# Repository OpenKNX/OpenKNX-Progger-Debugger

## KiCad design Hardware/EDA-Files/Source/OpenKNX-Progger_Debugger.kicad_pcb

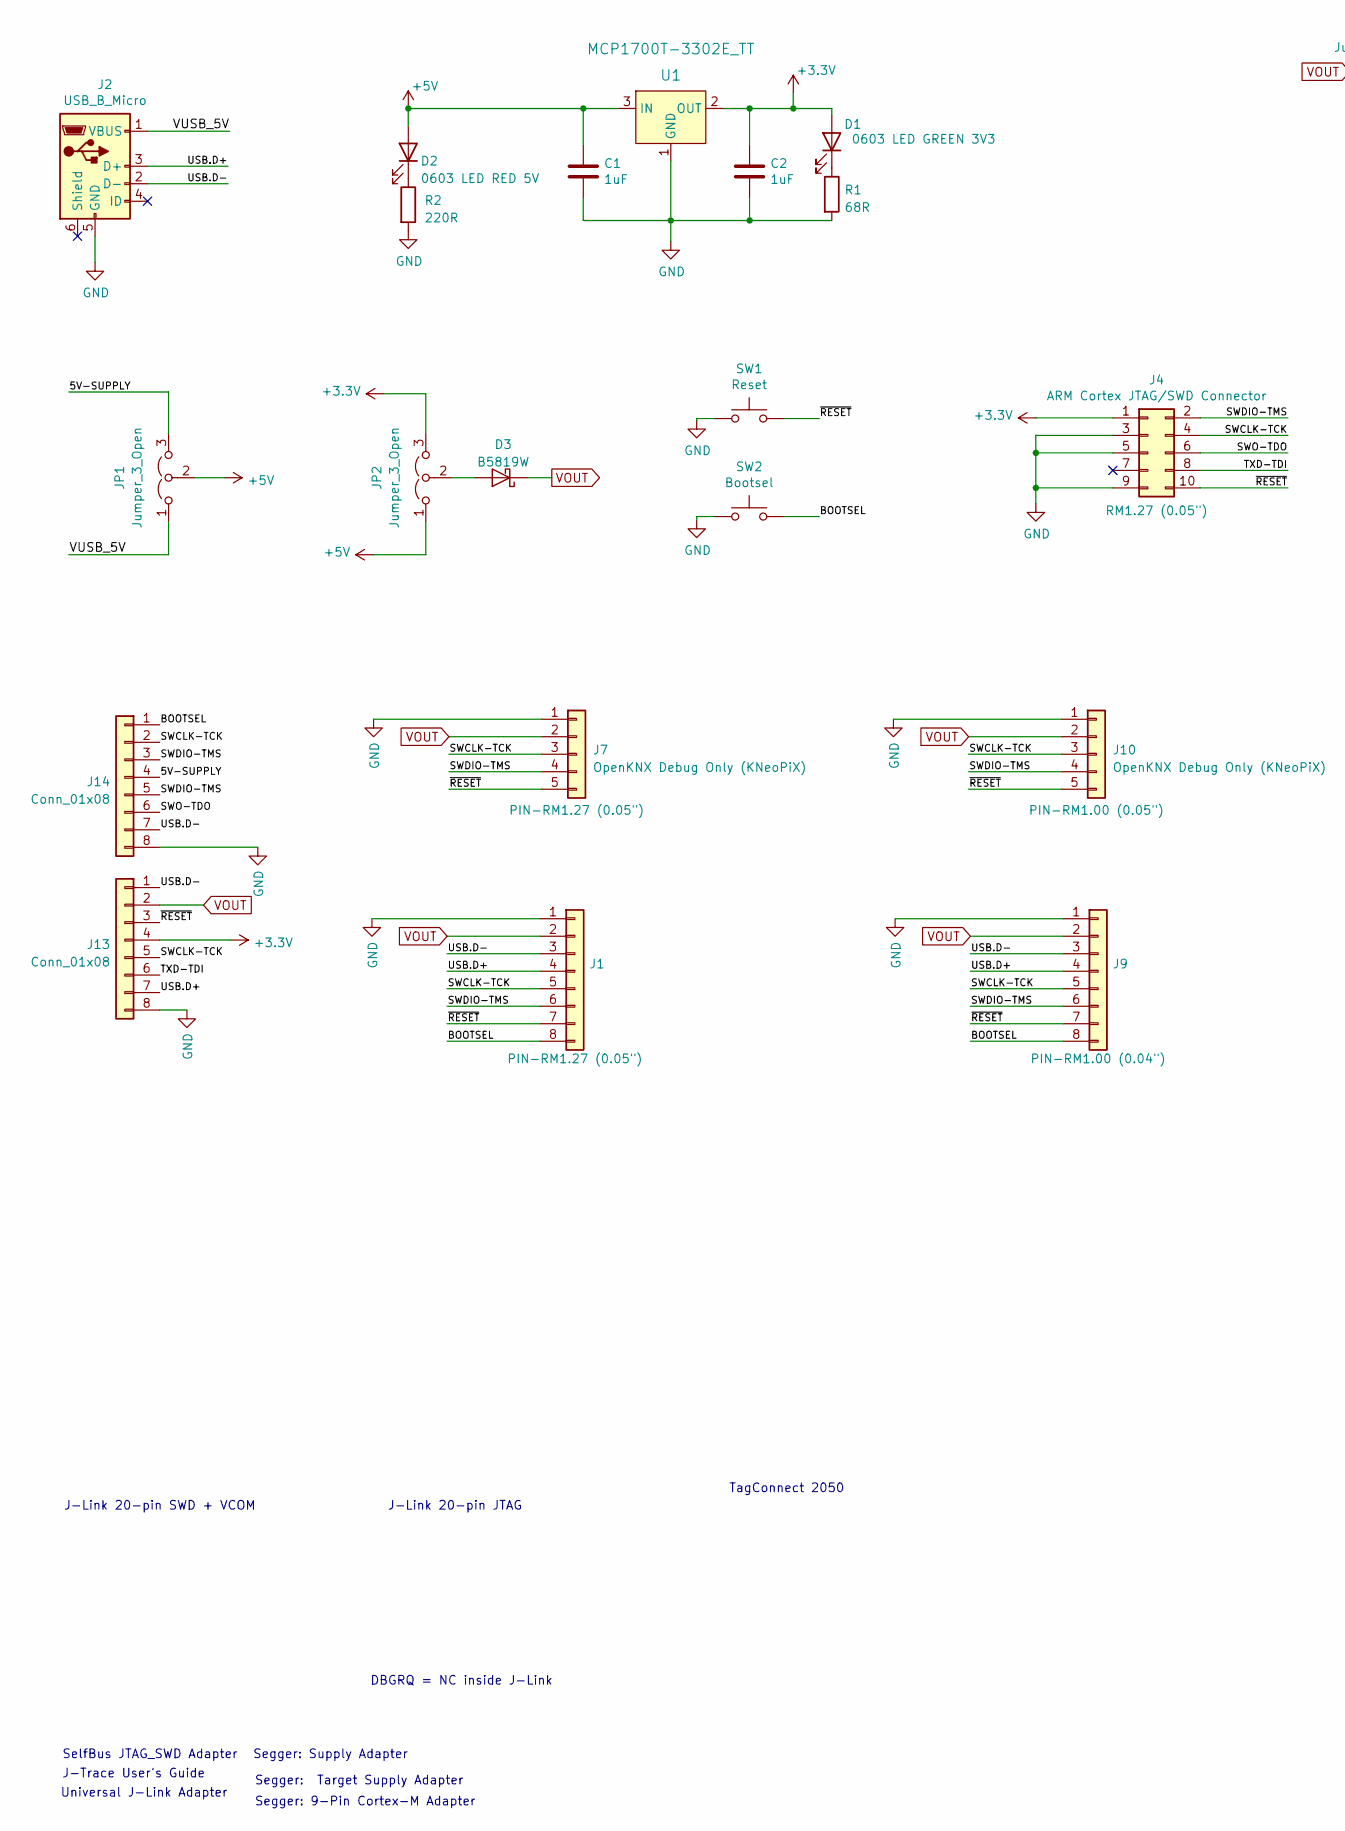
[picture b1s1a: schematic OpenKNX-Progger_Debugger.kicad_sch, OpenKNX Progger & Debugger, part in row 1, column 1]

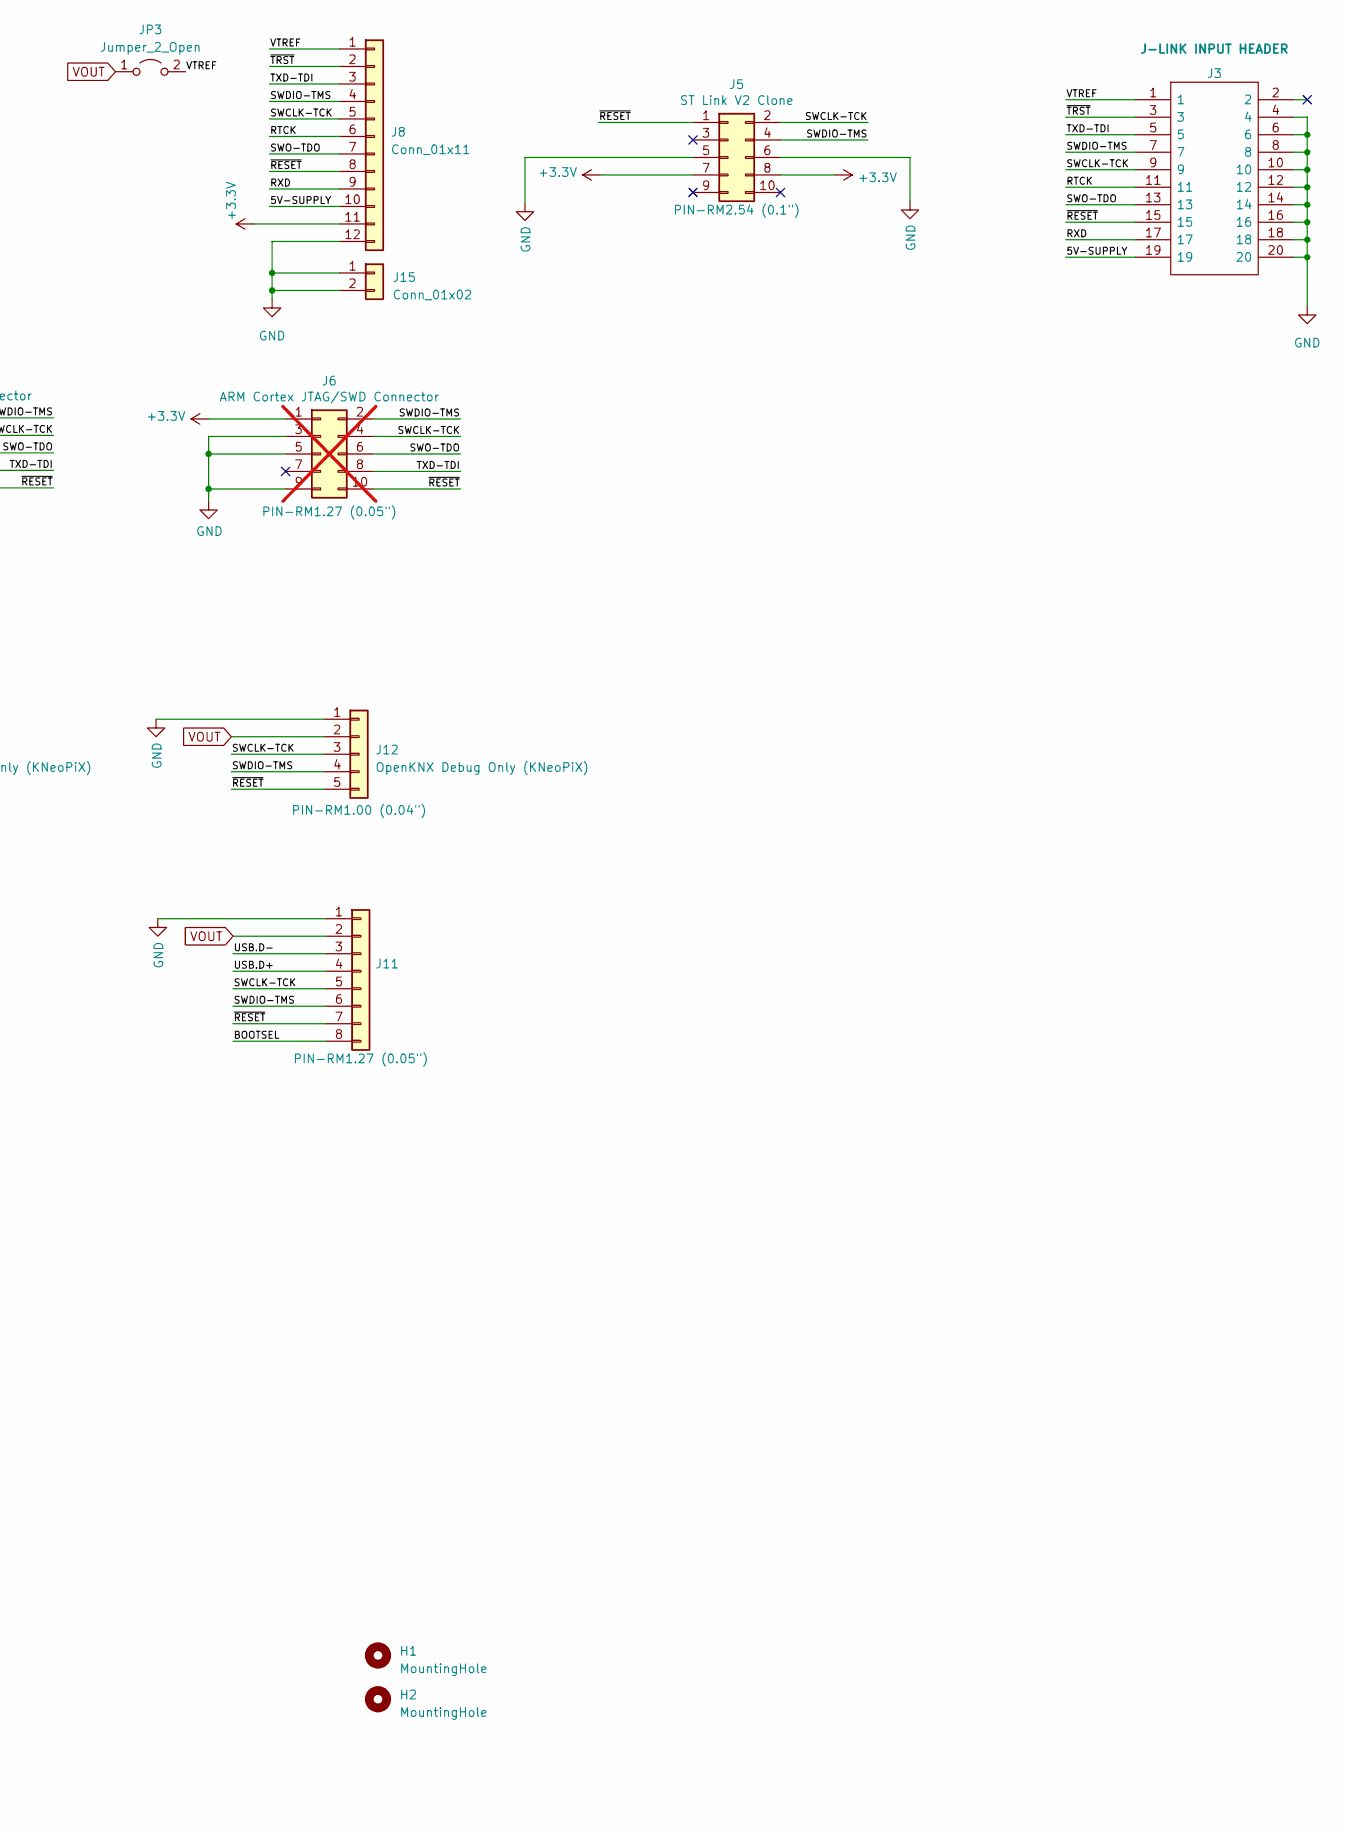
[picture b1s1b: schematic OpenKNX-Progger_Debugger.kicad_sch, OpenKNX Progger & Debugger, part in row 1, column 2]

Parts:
C1, C2: 1uF; C_0201_0603Metric_Pad0.64x0.40mm_HandSolder
D1: 0603 LED GREEN 3V3; LED_0201_0603Metric
D2: 0603 LED RED 5V; LED_0201_0603Metric
D3: B5819W; D_SOD-123; Part Number B140HW-7; JLCPCB ID C134429
H1, H2: MountingHole; MountingHole_2.1mm
J1, J11: OpenKNX Progger / Debugger Connection; PinSocket_1x08_P1.27mm_Vertical
J2: USB_B_Micro; USB_Micro-B_JING_C10418
J3: SFH11-PBPC-D10-RA-BK; IDC-Header_2x10_P2.54mm_Vertical; Manufacturer_Part_Number SFH11-PBPC-D10-RA-BK
J4: ARM Cortex JTAG/SWD Connector; PinHeader_2x05_P1.27mm_Vertical
J5: ST Link V2 Clone; IDC-Header_2x05_P2.54mm_Vertical
J6: ARM Cortex JTAG/SWD Connector; PinHeader_2x05_P1.27mm_Vertical; not fitted
J7, J12: OpenKNX Debug Only (KNeoPiX); PinSocket_1x05_P1.27mm_Vertical
J8: Conn_01x11; PinHeader_1x12_P2.54mm_Vertical
J9: OpenKNX Progger / Debugger Connection; JST_SHL_SM08B-SHLS-TF_1x08-1MP_P1.00mm_Horizontal
J10: OpenKNX Debug Only (KNeoPiX); JST_SHL_SM05B-SHLS-TF_1x05-1MP_P1.00mm_Horizontal
J13: Conn_01x08; JUMPER_SMD_1x8_NO_CUTS
J14: Conn_01x08; JUMPER_SMD_1x8_CUTS
J15: Conn_01x02; PinHeader_1x02_P2.54mm_Vertical
JP1, JP2: Jumper_3_Open; PinHeader_1x03_P1.27mm_Vertical
JP3: Jumper_2_Open; PinHeader_1x02_P1.27mm_Vertical
R1: 68R_0603_0.1%; R_0201_0603Metric
R2: 220R_0603_0.1%; R_0201_0603Metric
SW1: Reset; SW_Push_Xunpu_TS-1089S_Handsolder
SW2: Bootsel; SW_Push_Xunpu_TS-1089S_Handsolder
U1: MCP1700T-3302E_TT; SOT-23-3; MPN MCP1700T-3302E/TT; Digi-Key_PN MCP1700T3302ETTCT-ND

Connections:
+3.3V: C2.1, D1.2 (A), J4.1, J5.7, J5.8, J6.1, J8.11, J13.4, JP2.3 (B), U1.2 (OUT)
+5V: C1.1, D2.2 (A), JP1.2 (C), JP2.1 (A), U1.3 (IN)
/5V-SUPPLY: J3.19, J8.10, J14.4, JP1.3 (B)
/BOOTSEL: J1.8, J9.8, J11.8, J14.1, SW2.2
/RTCK: J3.11, J8.6
/RXD: J3.17, J8.9
/SWCLK-TCK: J1.5, J3.9, J4.4, J5.2, J7.3, J8.5, J9.5, J10.3, J11.5, J12.3, J13.5, J14.2
/SWDIO-TMS: J1.6, J3.7, J4.2, J5.4, J7.4, J8.4, J9.6, J10.4, J11.6, J12.4, J14.3, J14.5
/SWO-TDO: J1.13, J3.13, J4.6, J6.6, J8.7, J14.6
/TXD-TDI: J3.5, J4.8, J8.3, J13.6
/USB.D+: J1.4, J2.3 (D+), J9.4, J11.4, J13.7
/USB.D-: J1.3, J2.2 (D-), J9.3, J11.3, J13.1, J14.7
/VTREF: J3.1, J8.1, JP3.2 (B)
/VUSB_5V: J2.1 (VBUS), JP1.1 (A)
/~RESET: J1.7, J3.15, J4.10, J5.1, J7.5, J8.8, J9.7, J10.5, J11.7, J12.5, J13.3, SW1.2
/~TRST: J3.3, J8.2
GND: C1.2, C2.2, J1.1, J2.5 (GND), J3.4, J3.6, J3.8, J3.10, J3.12, J3.14, J3.16, J3.18, J3.20, J4.3, J4.5, J4.9, J5.5, J5.6, J7.1, J8.12, J9.1, J10.1, J11.1, J12.1, J13.8, J14.8, J15.1, J15.2, R1.2, R2.2, SW1.1, SW2.1, U1.1 (GND)
unnamed: D1.1 (K), R1.1
unnamed: D2.1 (K), R2.1
unnamed: D3.2 (A), JP2.2 (C)
VOUT: D3.1 (K), J1.2, J7.2, J9.2, J10.2, J11.2, J12.2, J13.2, JP3.1 (A)

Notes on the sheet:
DBGRQ = NC inside J-Link
J-Trace User's Guide
J-Link 20-pin SWD + VCOM
Segger: Target Supply Adapter
Segger: Supply Adapter
SelfBus JTAG_SWD Adapter
Segger: 9-Pin Cortex-M Adapter
J-Link 20-pin JTAG
Universal J-Link Adapter
TagConnect 2050

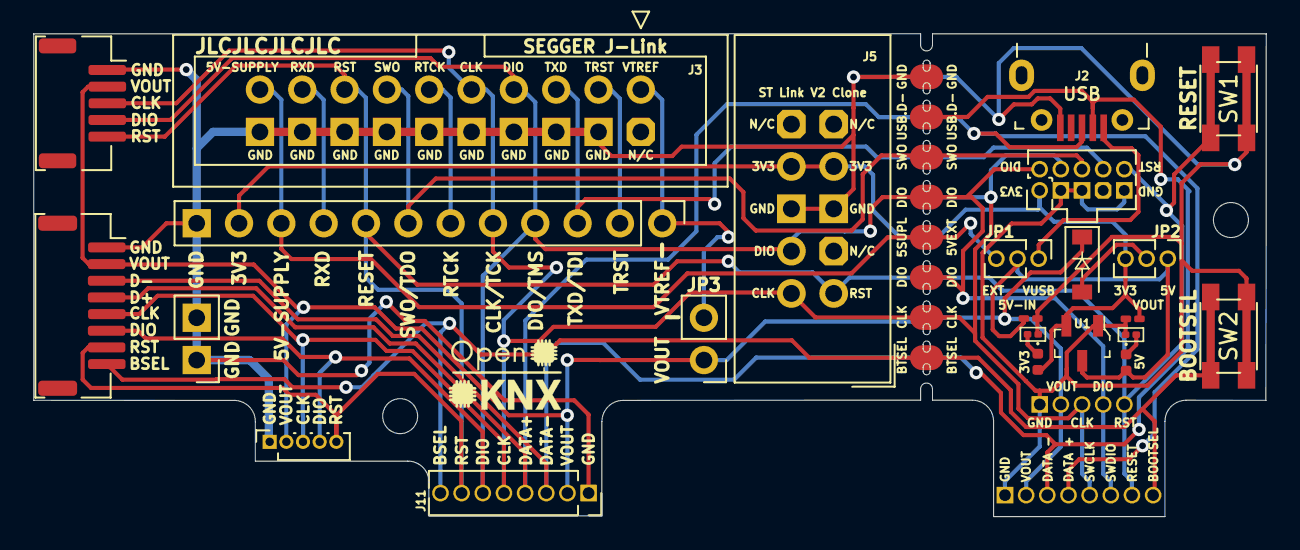
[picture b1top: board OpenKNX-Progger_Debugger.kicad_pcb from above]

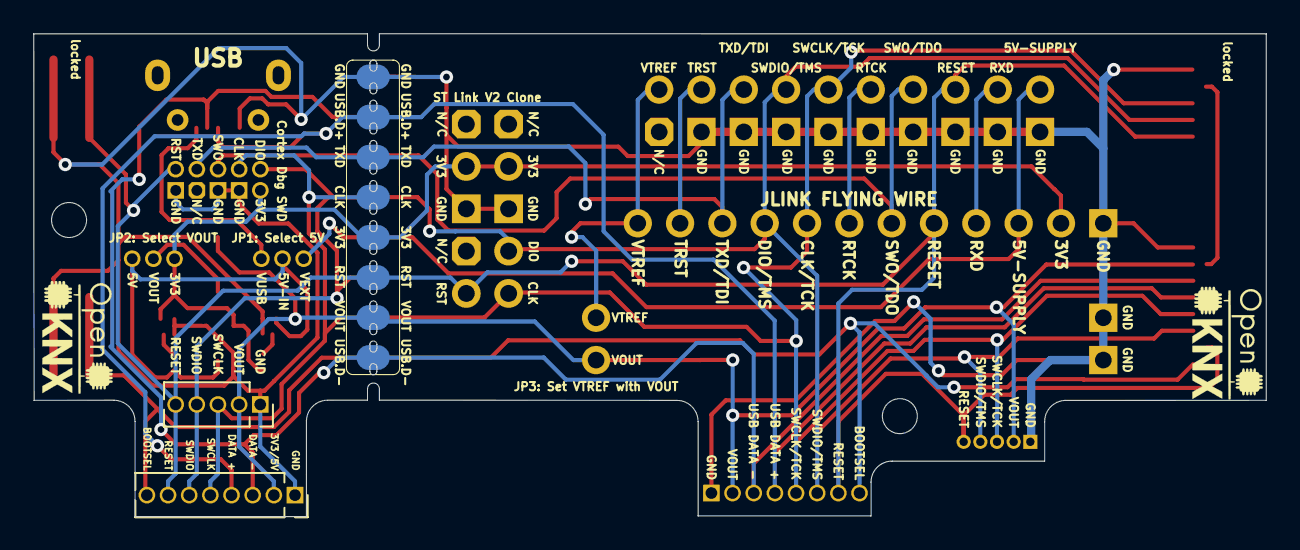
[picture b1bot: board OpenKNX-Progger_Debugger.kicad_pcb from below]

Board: 2 copper layers, 74.0 x 29.0 mm, 29 parts (3 on the bottom side), 21 nets.

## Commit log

2023-09-03 Initial OpenKNX commit
2023-09-06 Fixed PageLayout
    - fixed PageLayout "text"
2023-10-14 Initial - OpenKNX Debugger and programmer Case
    - New Desk-Case
    - Some folder & file cleanups

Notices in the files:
Hardware/EDA-Files/Source/OpenKNX-Progger_Debugger.kicad_pcb:
Erkan Çolak © 2023
